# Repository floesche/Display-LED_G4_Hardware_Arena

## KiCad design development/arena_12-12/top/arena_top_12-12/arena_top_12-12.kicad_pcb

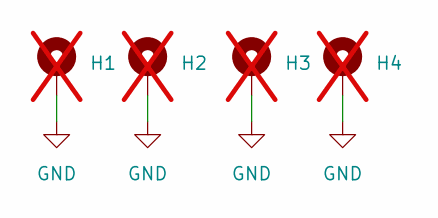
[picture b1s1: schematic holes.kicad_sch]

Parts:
H1, H2, H3, H4: MountingHole_Pad; MountingHole_4.5mm_Pad; not fitted

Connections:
GND: H1.1, H2.1, H3.1, H4.1; also elsewhere on the board

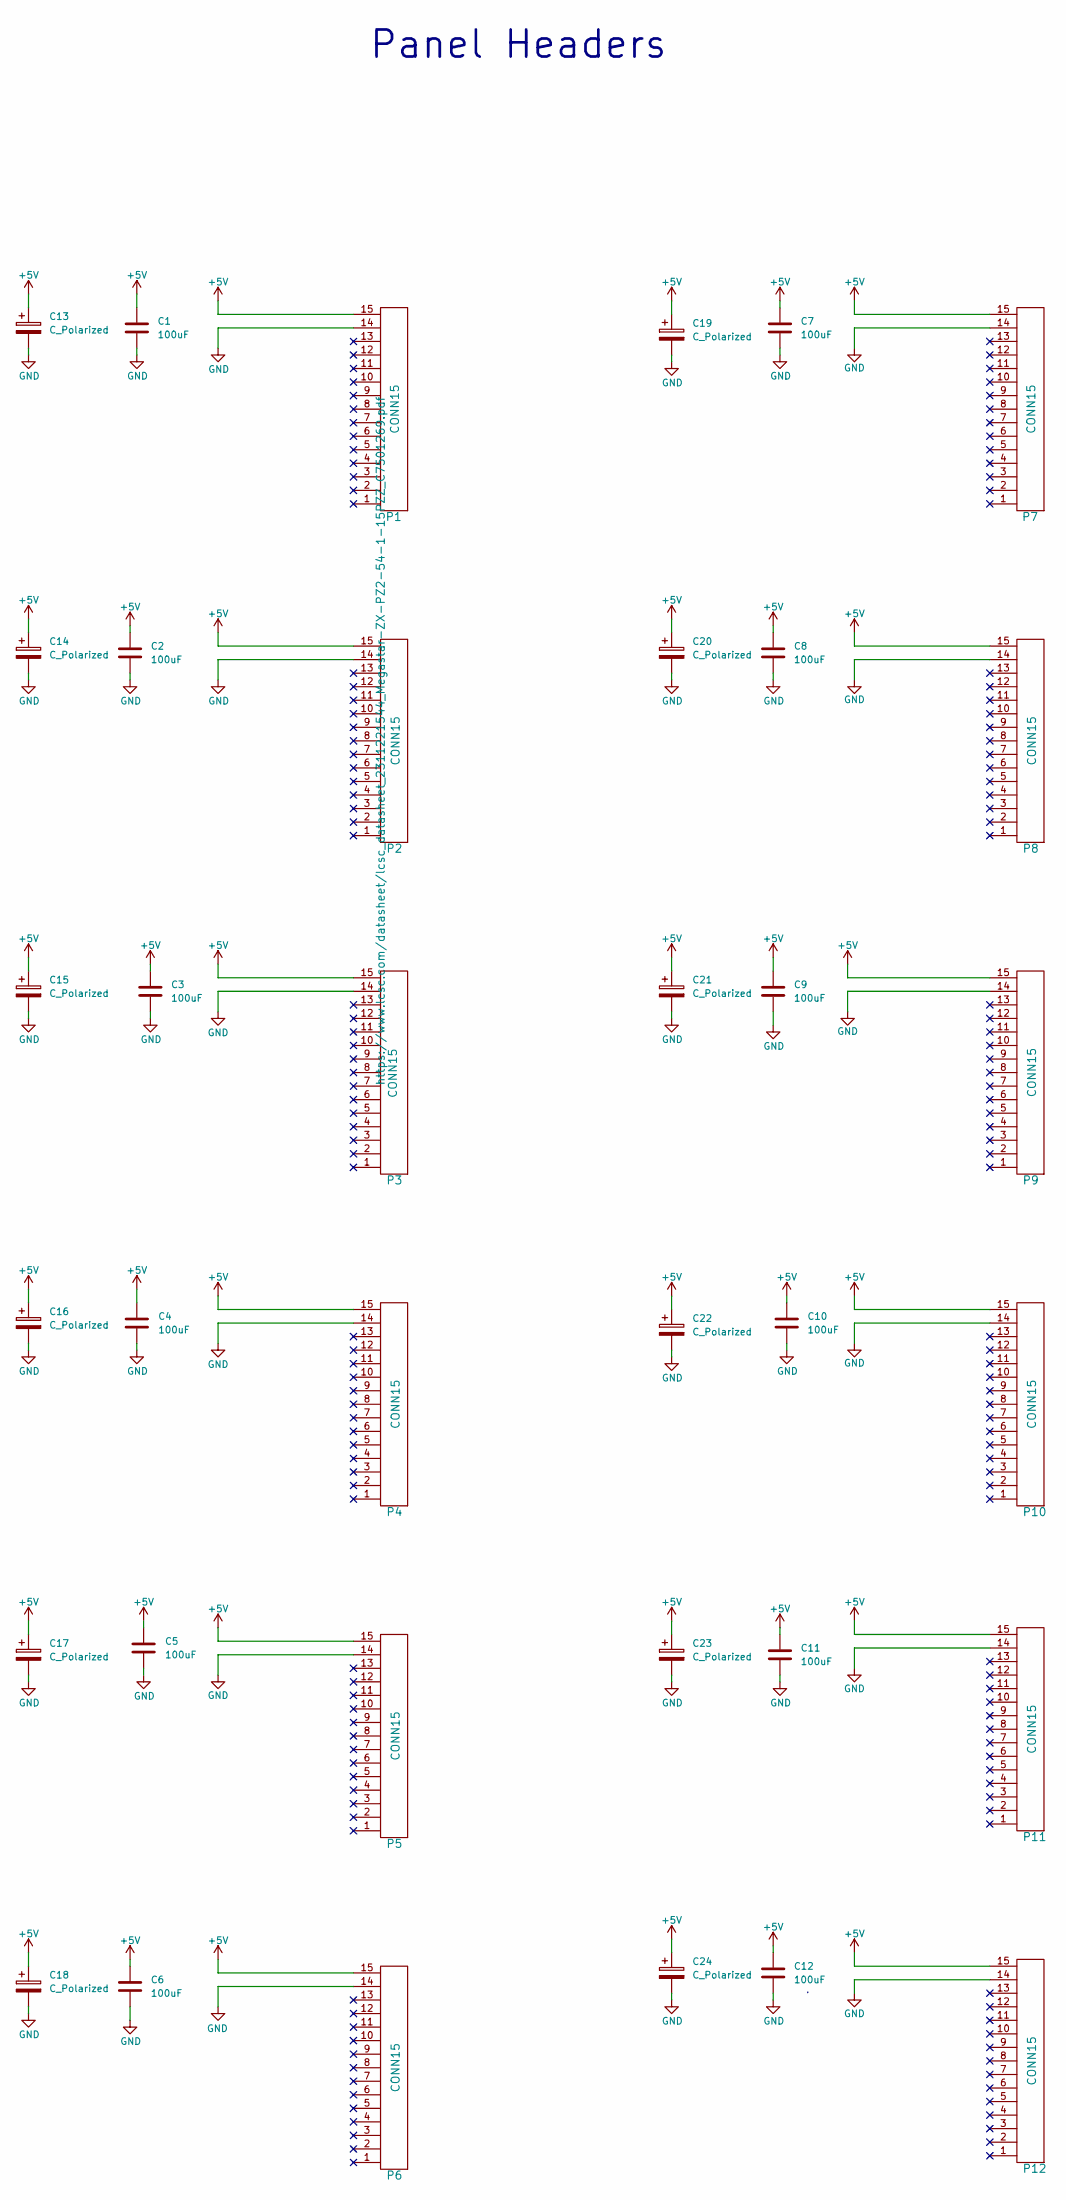
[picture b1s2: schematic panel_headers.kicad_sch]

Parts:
C1, C2, C3, C4, C5, C6, C7, C8, C9, C10, C11, C12: 100uF; C_1210_3225Metric; MPN HGC1210R5107M160NSVK; LCSC Part # C7432790
C13, C14, C15, C16, C17, C18, C19, C20, C21, C22, C23, C24: C_Polarized; CP_Radial_D8.0mm_P2.50mm; MPN 16YXF100MEFC6.3X11; DigiKey PN 1189-1856-ND
P1, P2, P3, P4, P5, P6, P7, P8, P9, P10, P11, P12: CONN15; HEADER_TOP; MPN PRPC040SAAN-RC; DigiKey PN S1011EC-40-ND

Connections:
+5V: C1.1, C2.1, C3.1, C4.1, C5.1, C6.1, C7.1, C8.1, C9.1, C10.1, C11.1, C12.1, C13.1, C14.1, C15.1, C16.1, C17.1, C18.1, C19.1, C20.1, C21.1, C22.1, C23.1, C24.1, P1.15, P2.15, P3.15, P4.15, P5.15, P6.15, P7.15, P8.15, P9.15, P10.15, P11.15, P12.15; also elsewhere on the board
GND: C1.2, C2.2, C3.2, C4.2, C5.2, C6.2, C7.2, C8.2, C9.2, C10.2, C11.2, C12.2, C13.2, C14.2, C15.2, C16.2, C17.2, C18.2, C19.2, C20.2, C21.2, C22.2, C23.2, C24.2, P1.14, P2.14, P3.14, P4.14, P5.14, P6.14, P7.14, P8.14, P9.14, P10.14, P11.14, P12.14; also elsewhere on the board

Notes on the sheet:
Panel Headers

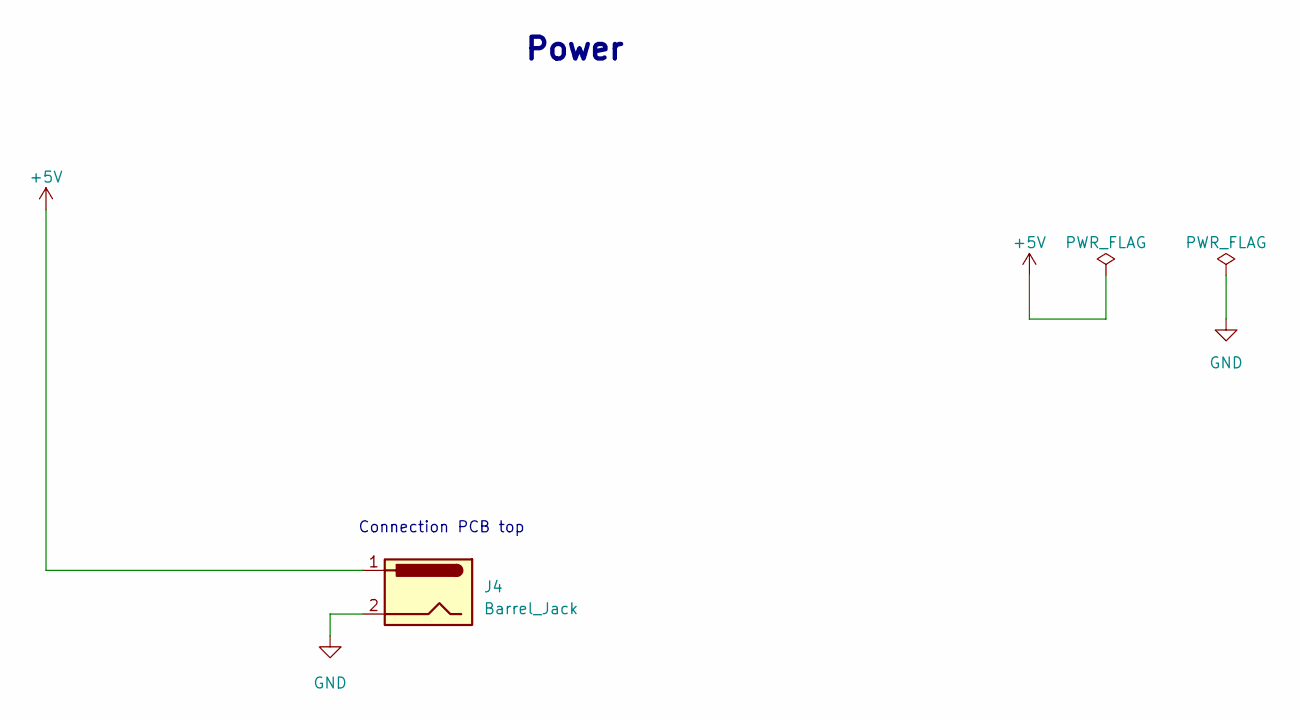
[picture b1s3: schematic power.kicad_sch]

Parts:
J4: Barrel_Jack; DCJACK_2PIN_HIGHCURRENT; MPN PJ-063AH; DigiKey PN CP-063AH-ND

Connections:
+5V: J4.1; also elsewhere on the board
GND: J4.2; also elsewhere on the board

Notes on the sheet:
Connection PCB top
Power

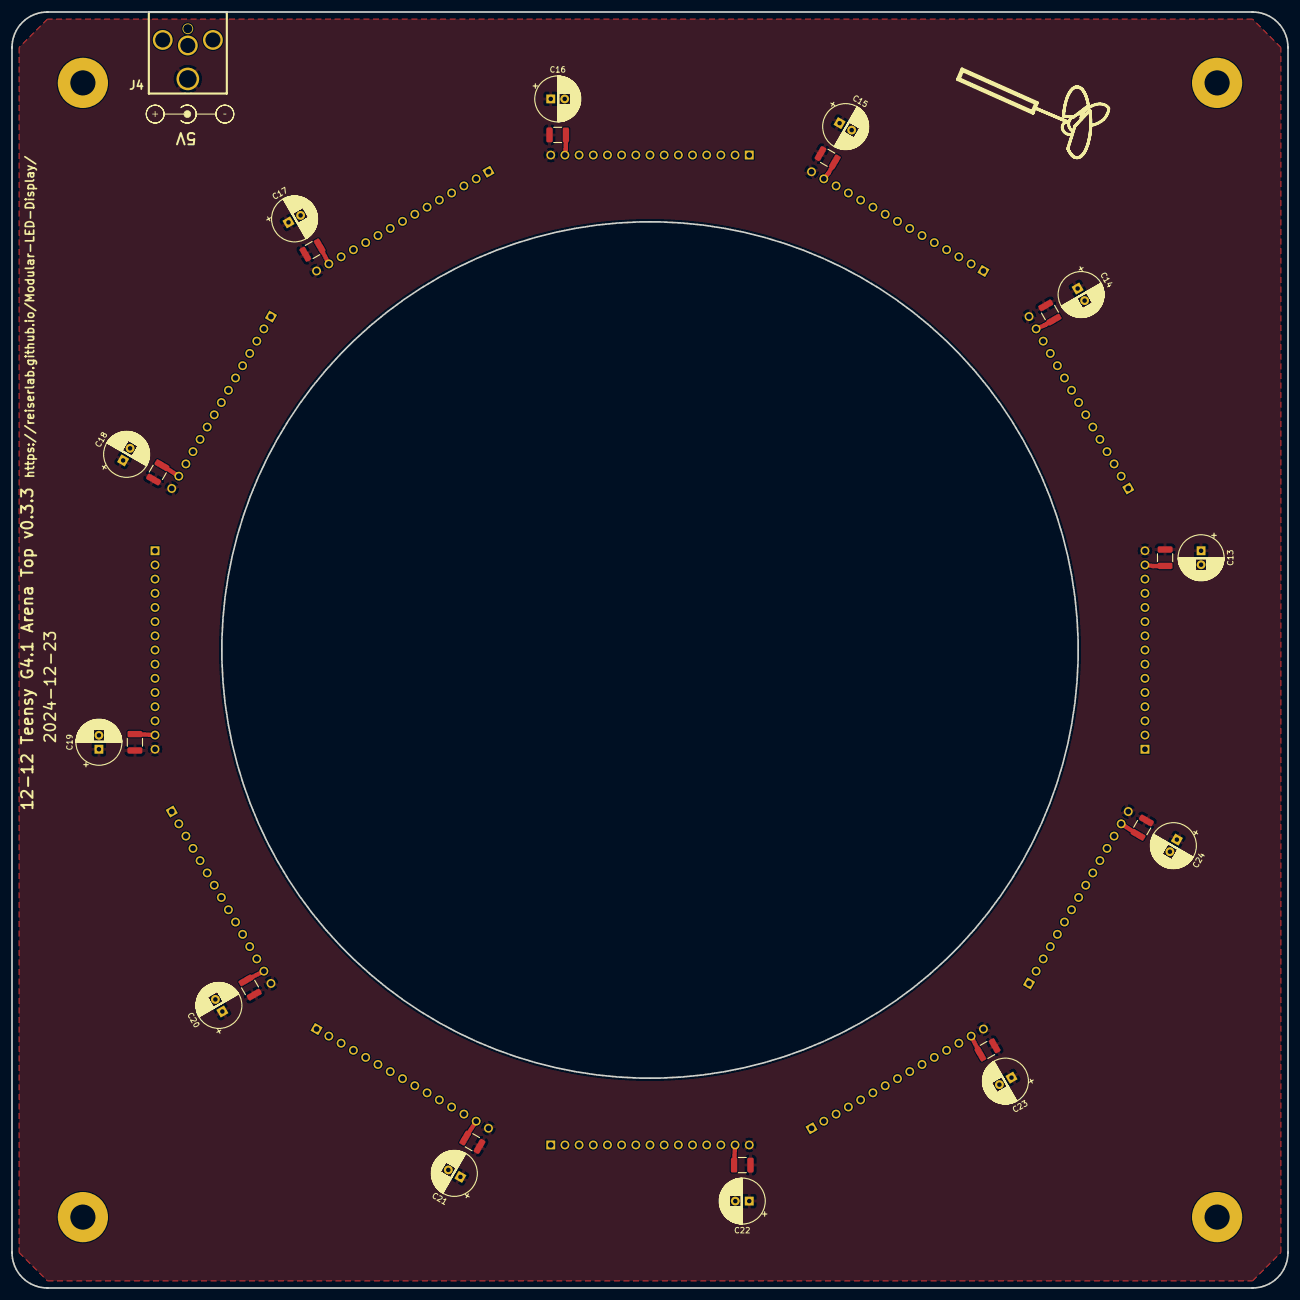
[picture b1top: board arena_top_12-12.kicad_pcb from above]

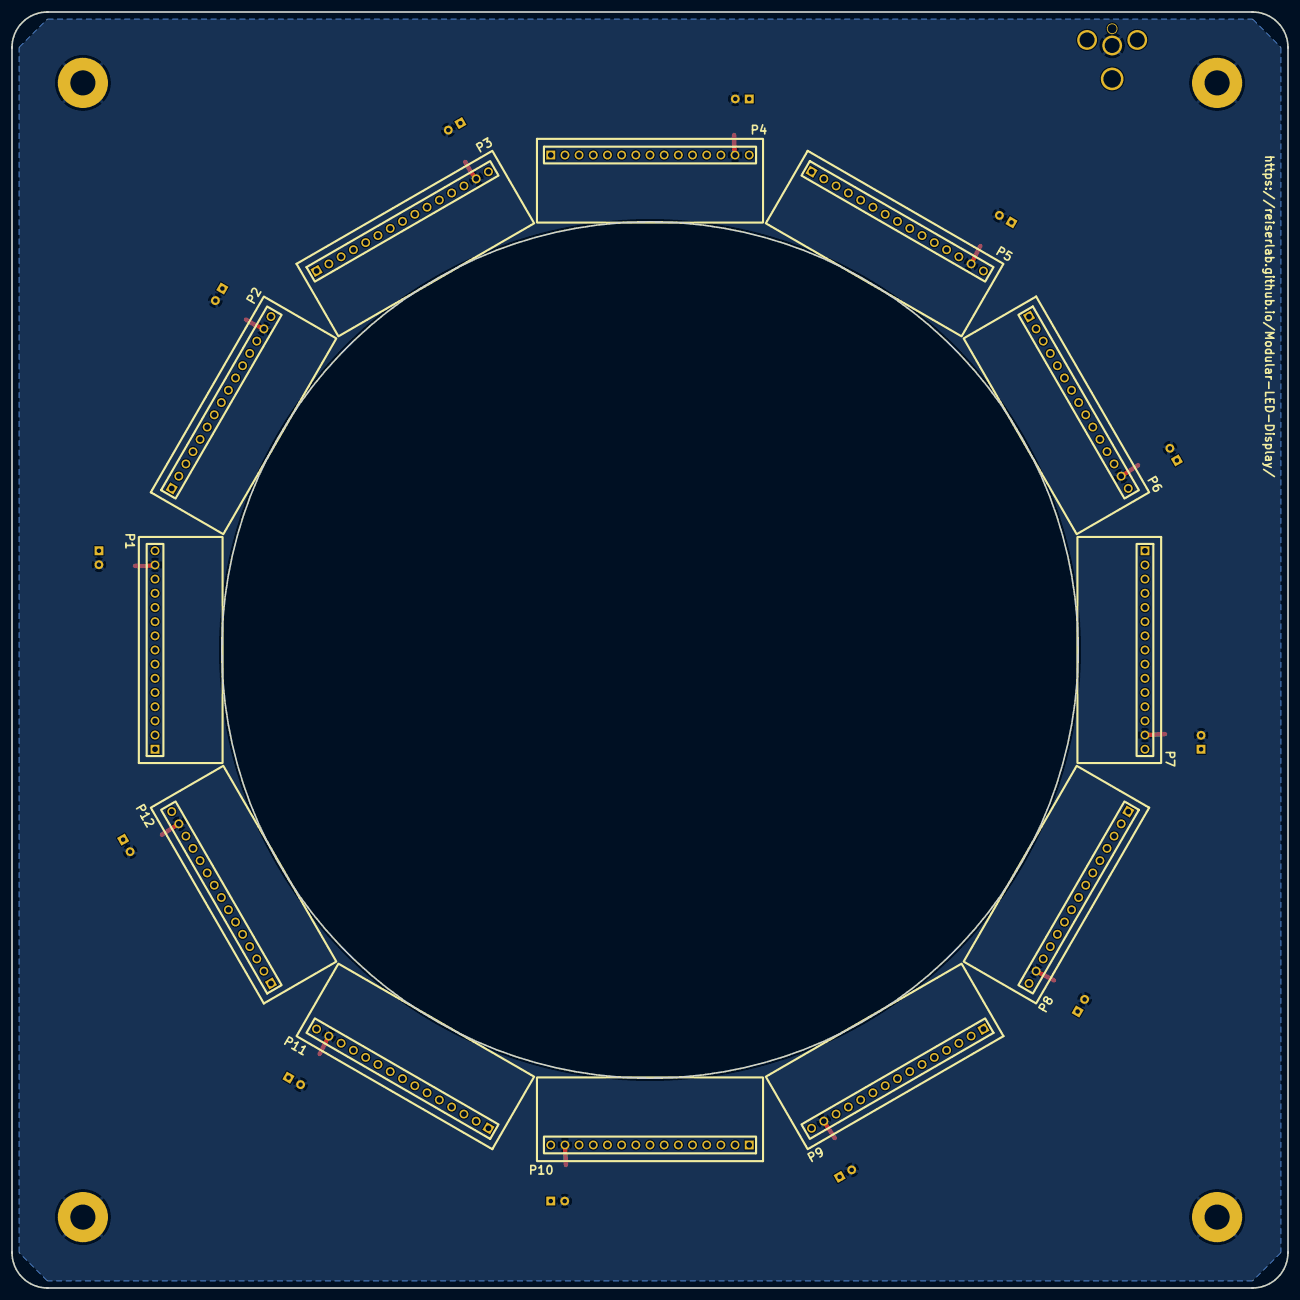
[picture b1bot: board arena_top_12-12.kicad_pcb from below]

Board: 2 copper layers, 228.6 x 228.6 mm, 41 parts (12 on the bottom side), 2 nets.

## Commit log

2023-08-03 update top acrylic 11-18
2024-12-23 rename to prepare merge with IORodeo
2024-12-23 pull development directory from IORodeo
2024-12-23 add top arena
2024-12-23 bump buffer version to 0.2
2024-12-23 first step cleanup
2024-12-23 bump version to 0.3
2024-12-23 export for production
2024-12-23 cleanup top
2024-12-23 update schema pdfs
